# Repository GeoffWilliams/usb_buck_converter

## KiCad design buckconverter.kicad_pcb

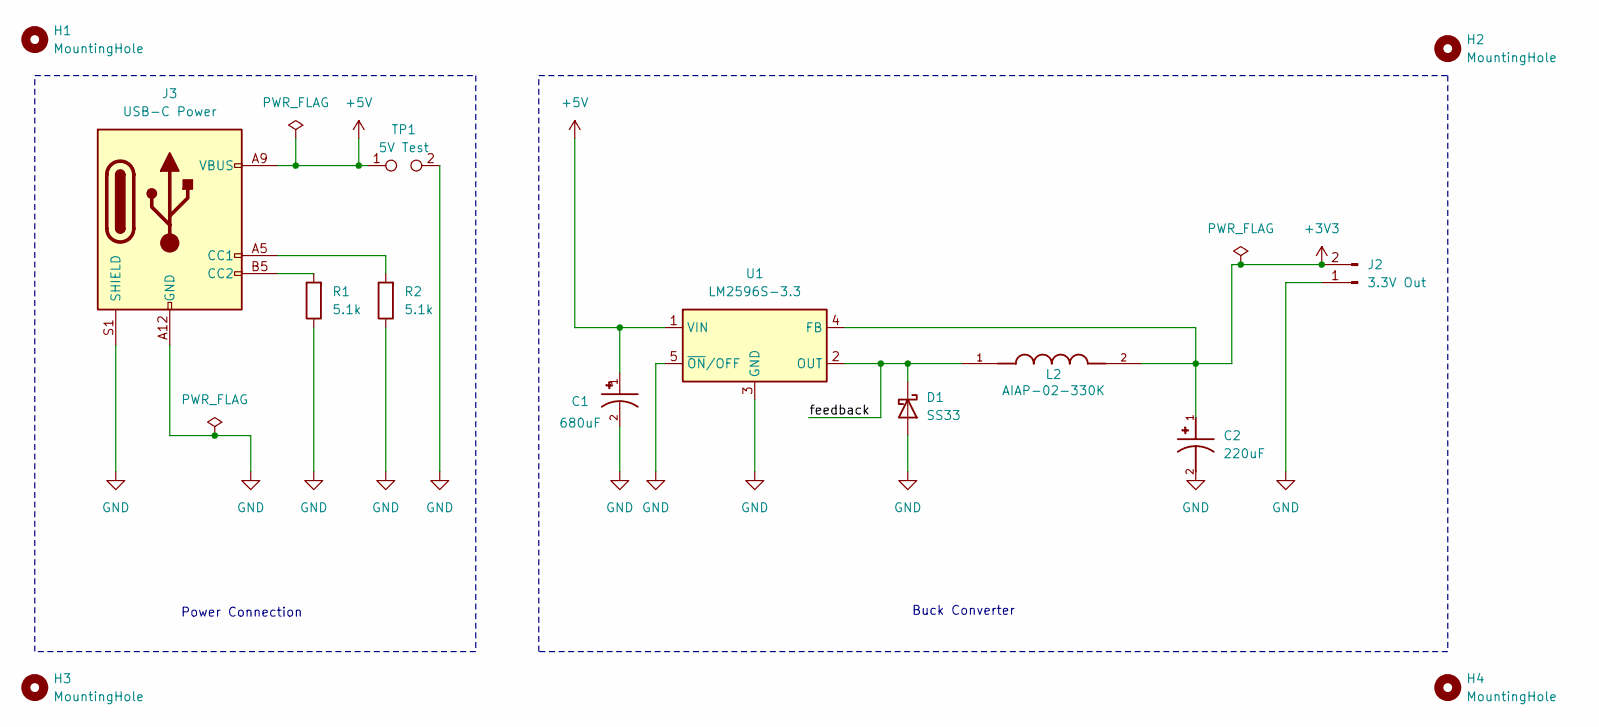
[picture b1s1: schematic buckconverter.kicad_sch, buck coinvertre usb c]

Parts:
C1: 680uF; CAP_EEEFK1J681AM; PARTREV 10-Oct-19
C2: 220uF; CAPMP7343X430N; PARTREV N/A
D1: SS33; D_SMA
H1, H2, H3, H4: MountingHole; MountingHole_3.2mm_M3
J2: 3.3V Out; PinHeader_1x02_P2.54mm_Vertical
J3: USB-C Power; USB_C_Receptacle_GCT_USB4125-xx-x-0190_6P_TopMnt_Horizontal
L2: AIAP-02-330K; INDAD1880W80L1400D680; PARTREV 10/29/2021
R1, R2: 5.1k; R_0603_1608Metric
TP1: 5V Test; TestPoint_2Pads_Pitch2.54mm_Drill0.8mm
U1: LM2596S-3.3; TO-263-5_TabPin3

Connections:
+3V3: C2.1, J2.2, L2.2, U1.4 (FB)
+5V: C1.1, J3.A9 (VBUS), J3.B9 (VBUS), TP1.1, U1.1 (VIN)
/feedback: D1.1 (K), L2.1, U1.2 (OUT)
GND: C1.2, C2.2, D1.2 (A), J2.1, J3.A12 (GND), J3.B12 (GND), J3.S1 (SHIELD), R1.1, R2.1, TP1.2, U1.3 (GND), U1.5 (~ON/OFF)
unnamed: J3.A5 (CC1), R2.2
unnamed: J3.B5 (CC2), R1.2

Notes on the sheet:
Buck Converter
Power Connection

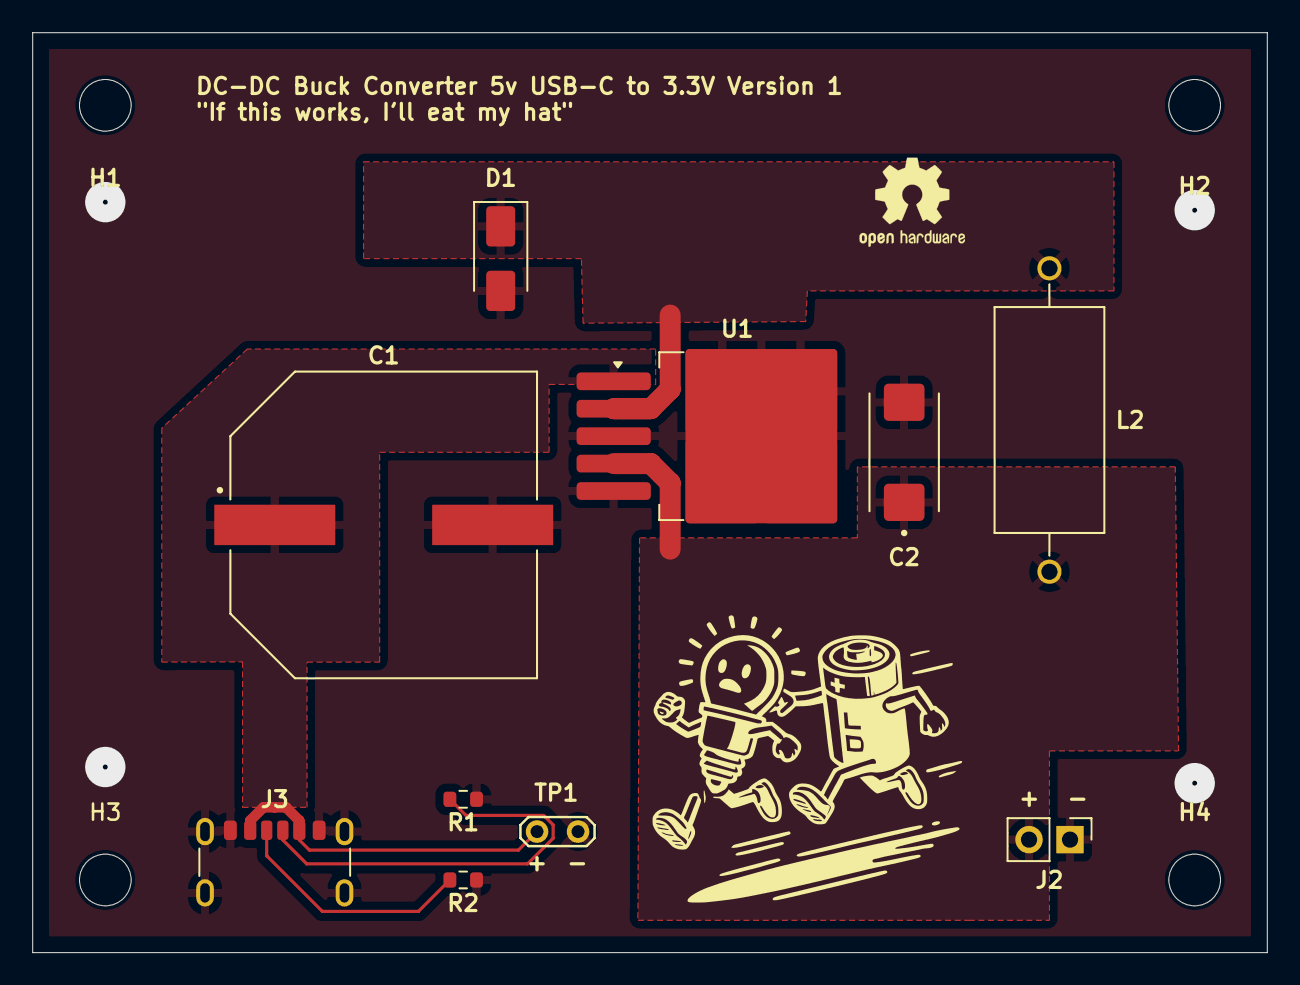
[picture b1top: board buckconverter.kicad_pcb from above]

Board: 2 copper layers, 76.5 x 57.0 mm, 14 parts (0 on the bottom side), 6 nets.

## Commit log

2024-10-24 initial
2024-10-25 feedbacks: dont trace thru copper fill, move caps closer, add vias
2024-10-25 drc fixes
2024-10-25 move copper fill further from grounds
